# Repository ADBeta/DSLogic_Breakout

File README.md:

# DSLogic 16-Channel Breakout

## Description
A Breakout board for the 16-Channel DSLogic Logic Analyzers, which breaks the
1.27mm pitch headers out into a 2.54mm pin header, and includes an area  for
protoboarding!  

## Gallery

## Parts List
`D1           Any 0603 LED`  
`R1           2.2K 0603 Resistor`  
`RN1 - RN4    1206 100K Resistor Array`  
`J1           1.27mm 02x20 Male Pin Header`  
`J2           2.56mm 01x20 Male Pin Header (Optional)`  

## Dimensions
54mm x 56mm, 0.8mm Thickness

----
Copyright (c) ADBeta 2024

This program is free software; you can redistribute it and/or modify it under
the terms of the GNU General Public License as published by the Free Software
Foundation; either version 2 of the License, 
or (at your option) any later version.

This program is distributed in the hope that it will be useful, but 
WITHOUT ANY WARRANTY; without even the implied warranty of MERCHANTABILITY or
FITNESS FOR A PARTICULAR PURPOSE.  
See the GNU General Public License for more details.

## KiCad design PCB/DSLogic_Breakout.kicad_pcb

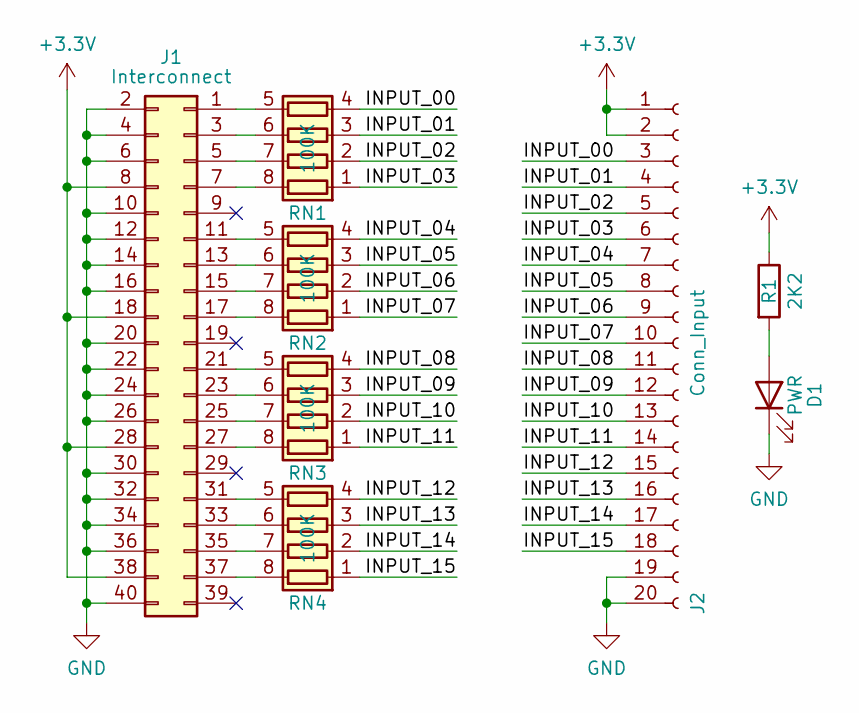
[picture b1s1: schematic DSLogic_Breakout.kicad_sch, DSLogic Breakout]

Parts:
D1: PWR; LED_0603_1608Metric
J1: Interconnect; PinHeader_2x20_P1.27_Dual_Sided
J2: Conn_Input; PinSocket_1x20_P2.54mm_Vertical
R1: 2K2; R_0603_1608Metric
RN1, RN2, RN3, RN4: 100K; R_Array_Convex_4x0603

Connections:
+3.3V: J1.8, J1.18, J1.28, J1.38, J2.1, J2.2, R1.1
/INPUT_00: J2.3, RN1.4 (R4.1)
/INPUT_01: J2.4, RN1.3 (R3.1)
/INPUT_02: J2.5, RN1.2 (R2.1)
/INPUT_03: J2.6, RN1.1 (R1.1)
/INPUT_04: J2.7, RN2.4 (R4.1)
/INPUT_05: J2.8, RN2.3 (R3.1)
/INPUT_06: J2.9, RN2.2 (R2.1)
/INPUT_07: J2.10, RN2.1 (R1.1)
/INPUT_08: J2.11, RN3.4 (R4.1)
/INPUT_09: J2.12, RN3.3 (R3.1)
/INPUT_10: J2.13, RN3.2 (R2.1)
/INPUT_11: J2.14, RN3.1 (R1.1)
/INPUT_12: J2.15, RN4.4 (R4.1)
/INPUT_13: J2.16, RN4.3 (R3.1)
/INPUT_14: J2.17, RN4.2 (R2.1)
/INPUT_15: J2.18, RN4.1 (R1.1)
GND: D1.1 (K), J1.2, J1.4, J1.6, J1.10, J1.12, J1.14, J1.16, J1.20, J1.22, J1.24, J1.26, J1.30, J1.32, J1.34, J1.36, J1.40, J2.19, J2.20
unnamed: D1.2 (A), R1.2
unnamed: J1.1, RN1.5 (R4.2)
unnamed: J1.3, RN1.6 (R3.2)
unnamed: J1.5, RN1.7 (R2.2)
unnamed: J1.7, RN1.8 (R1.2)
unnamed: J1.11, RN2.5 (R4.2)
unnamed: J1.13, RN2.6 (R3.2)
unnamed: J1.15, RN2.7 (R2.2)
unnamed: J1.17, RN2.8 (R1.2)
unnamed: J1.21, RN3.5 (R4.2)
unnamed: J1.23, RN3.6 (R3.2)
unnamed: J1.25, RN3.7 (R2.2)
unnamed: J1.27, RN3.8 (R1.2)
unnamed: J1.31, RN4.5 (R4.2)
unnamed: J1.33, RN4.6 (R3.2)
unnamed: J1.35, RN4.7 (R2.2)
unnamed: J1.37, RN4.8 (R1.2)

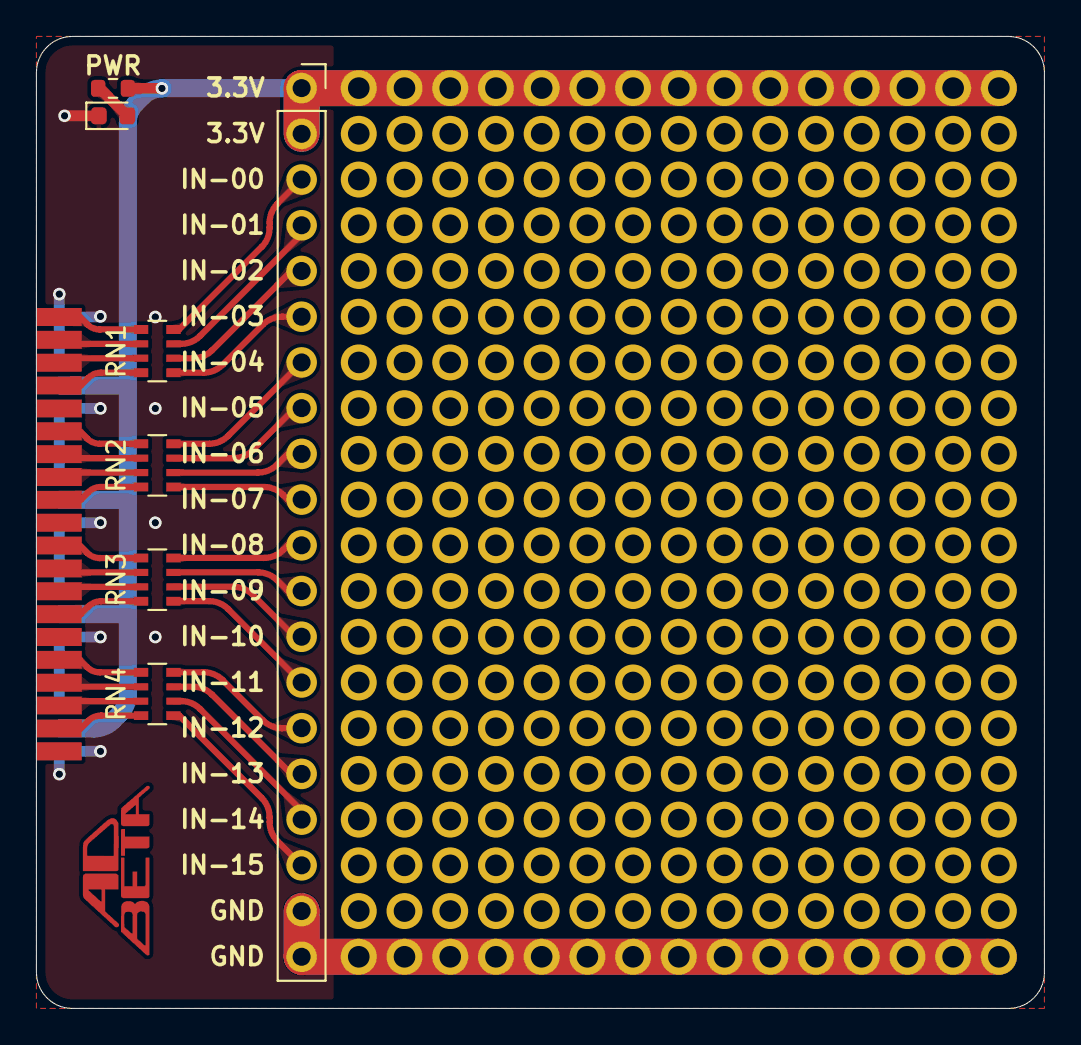
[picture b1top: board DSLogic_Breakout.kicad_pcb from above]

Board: 2 copper layers, 56.0 x 54.0 mm, 8 parts (0 on the bottom side), 35 nets.

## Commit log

2024-06-27 Board max size measured
2024-06-29 Rev 1 Done
2024-06-29 Added Images
2024-06-29 Fixed Readme
